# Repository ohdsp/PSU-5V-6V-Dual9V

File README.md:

# [Open Hardware DSP Platform](http://www.ohdsp.org)
## Multi output power supply for OHDSP
### Revision 1.1
###### PSU-5V-6V-Dual9V (KiCad 4.0.2-stable)
---
# README
### Disclaimer
Copyright Paul Janicki 2016

Licensed under the TAPR Open Hardware License (www.tapr.org/OHL)

This documentation is distributed WITHOUT ANY EXPRESS OR IMPLIED WARRANTY, INCLUDING OF MERCHANTABILITY, SATISFACTORY QUALITY AND FITNESS FOR A PARTICULAR PURPOSE.

### What is this repository? ###

**Quick summary**

This is a power supply for use with OHDSP boards.

This power supply requires a single 9Vac input (around 500mA should be sufficient for simple systems). 

This power supply outputs one 5V, one 5V or 6V, and +/-9V. Be warned that each of the 5V and 6V rail should be able to deliver higher currents (up to 1A) without issue, but this will overload the input if you are not careful.

This repository contains the KiCad design files, manufacturing Gerber/drill files, and PDF/drawing files for this board.

### How do I get set up? ###

**Summary of set up**

1. Set your self up a directory on a local disk, something simple will make life easier (eg C:\Electronics on Windows as used here), but anywhere will do just fine.
2. Download the Kicad-Libs from [https://github.com/ohdsp/KiCad-Libs](https://github.com/ohdsp/KiCad-Libs) and place in C:\Electronics\Kicad-Libs (or your chosen folder)  
3. Create a OHDSP subdirectory in C:\Electronics (so C:\Electronics\OHDSP)
3. Download this project to C:\Electronics\OHDSP\PSU-5V-6V-Dual9V
4. Fire up Kicad
5. Open the main project file C:\Electronics\OHDSP\PSU-5V-6V-Dual9V\Schematics\PSU-5V-6V-Dual9V.pro
6. (Optional) Setup Pcbnew component library as below.
7. Do as you wish with the project, just keep it under TAPR Open Hardware License

Make sure your git setup doesn't exclude files used in the project (like .LIB files) or things may go wrong down the line.

**KiCad Library Configuration**

Note that you need to setup a Pcbnew library, but the eeschema libraries should work without any changes if you followed the instructions above.

To setup Pcbnew libraries:

In Pcbnew go to Preferences -> Footprint Libraries Manager. Under Global Libraries tab in the top list check if there is a nickname "MyKiCadLibs-Footprints" (usually at the end of the list). If there is but it points to the wrong place then change the Library Path to point to MyKiCadLibs-Footprints (eg C:\Electronics\KiCad-Libs\MyKiCadLibs-Footprints.pretty) folder for your setup. If this is missing you can use "Append with Wizard", choose "Files on my computer", click next, browse to library location (eg C:\Electronics\KiCad-Libs\MyKiCadLibs-Footprints.pretty) and select the folder MyKiCadLibs-Footprints.pretty, click next, check the Status column states OK and the Format is KiCad (if not re-download the library) and click next, then select "To global library configuration..." and click Finish.

To setup eeschema component libraries:
Either from KiCad project window go to Tools -> Run Library Editor OR under eeschema, go to Tools -> Library Editor. Then Preferences -> Component Libraries.

The top section "Component Library Files" should ideally contain only two libraries, the "power" library that ships with KiCad and "MyKiCadLibs-Lib" available from above. To setup MyKiCadLibs-Lib as a relative path under the "User defined search path" click add. Browse to the location of KiCad-Libs you download above (eg C:\Electronics\KiCad-Libs) and click "Select Folder". Say yes to add a relative path. Under component library files click add, browse to the KiCad-libs again (eg C:\Electronics\KiCad-Libs), select file "MyKiCadLibs-Lib.lib" and click open. MyKiCadLibs-lib should appear in the component library list with no path as it will be using the user defined search path set in the box below.

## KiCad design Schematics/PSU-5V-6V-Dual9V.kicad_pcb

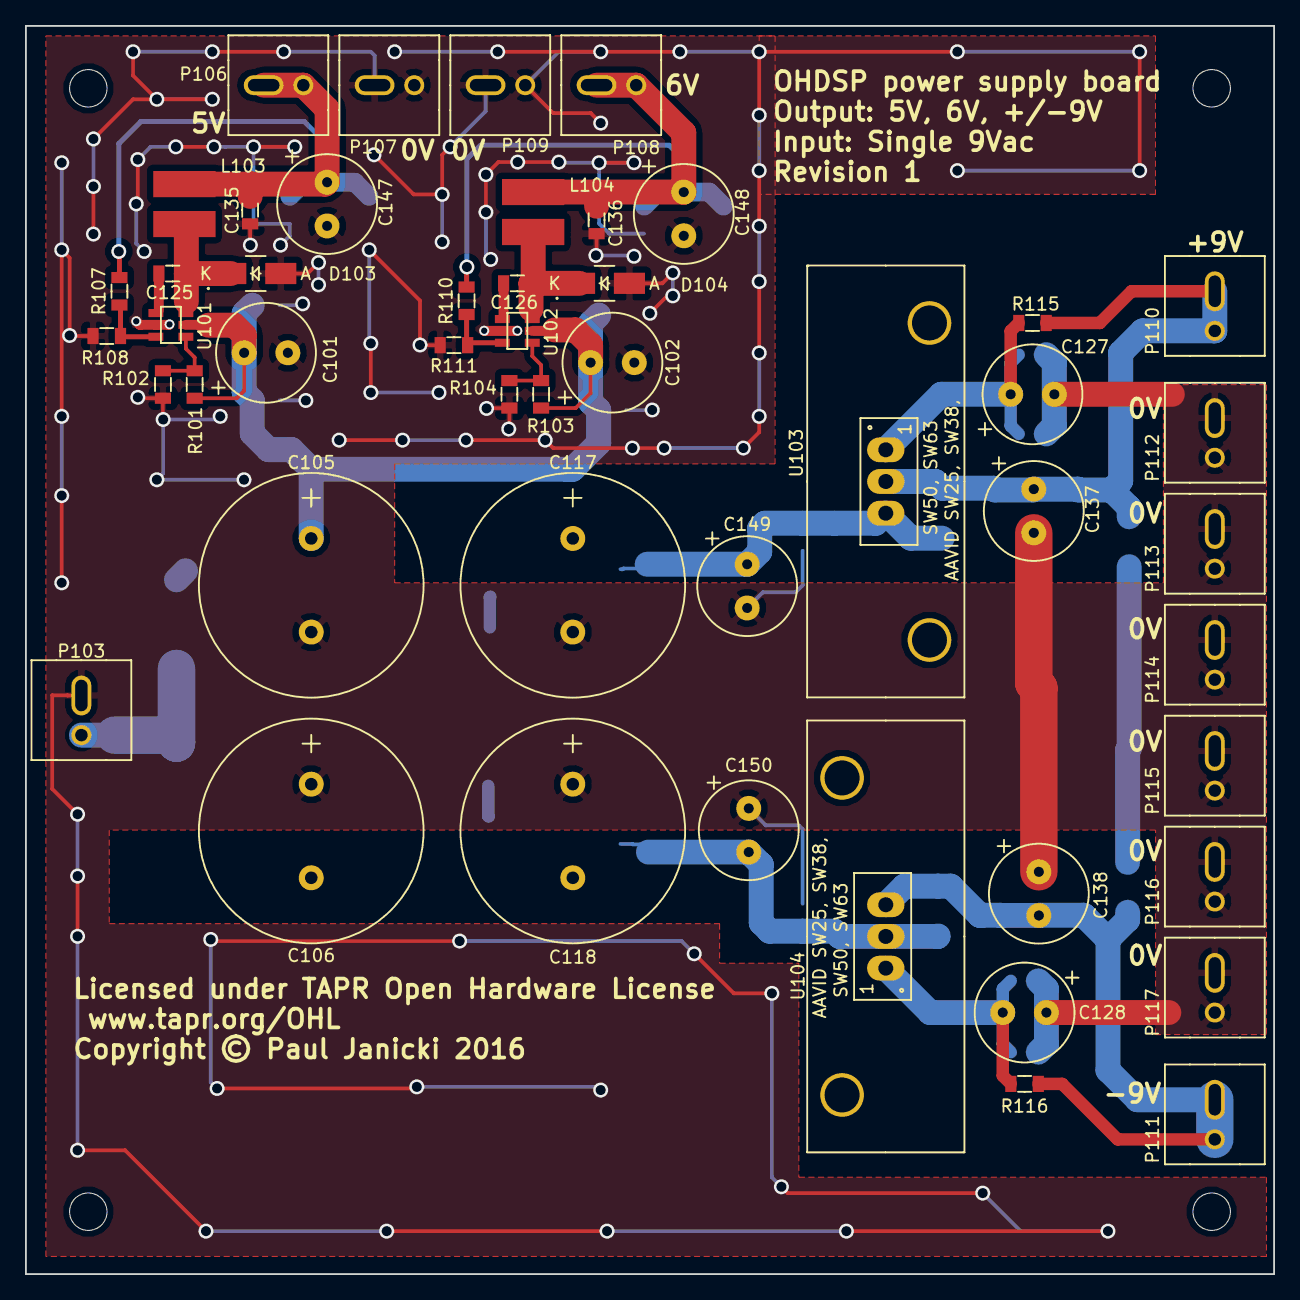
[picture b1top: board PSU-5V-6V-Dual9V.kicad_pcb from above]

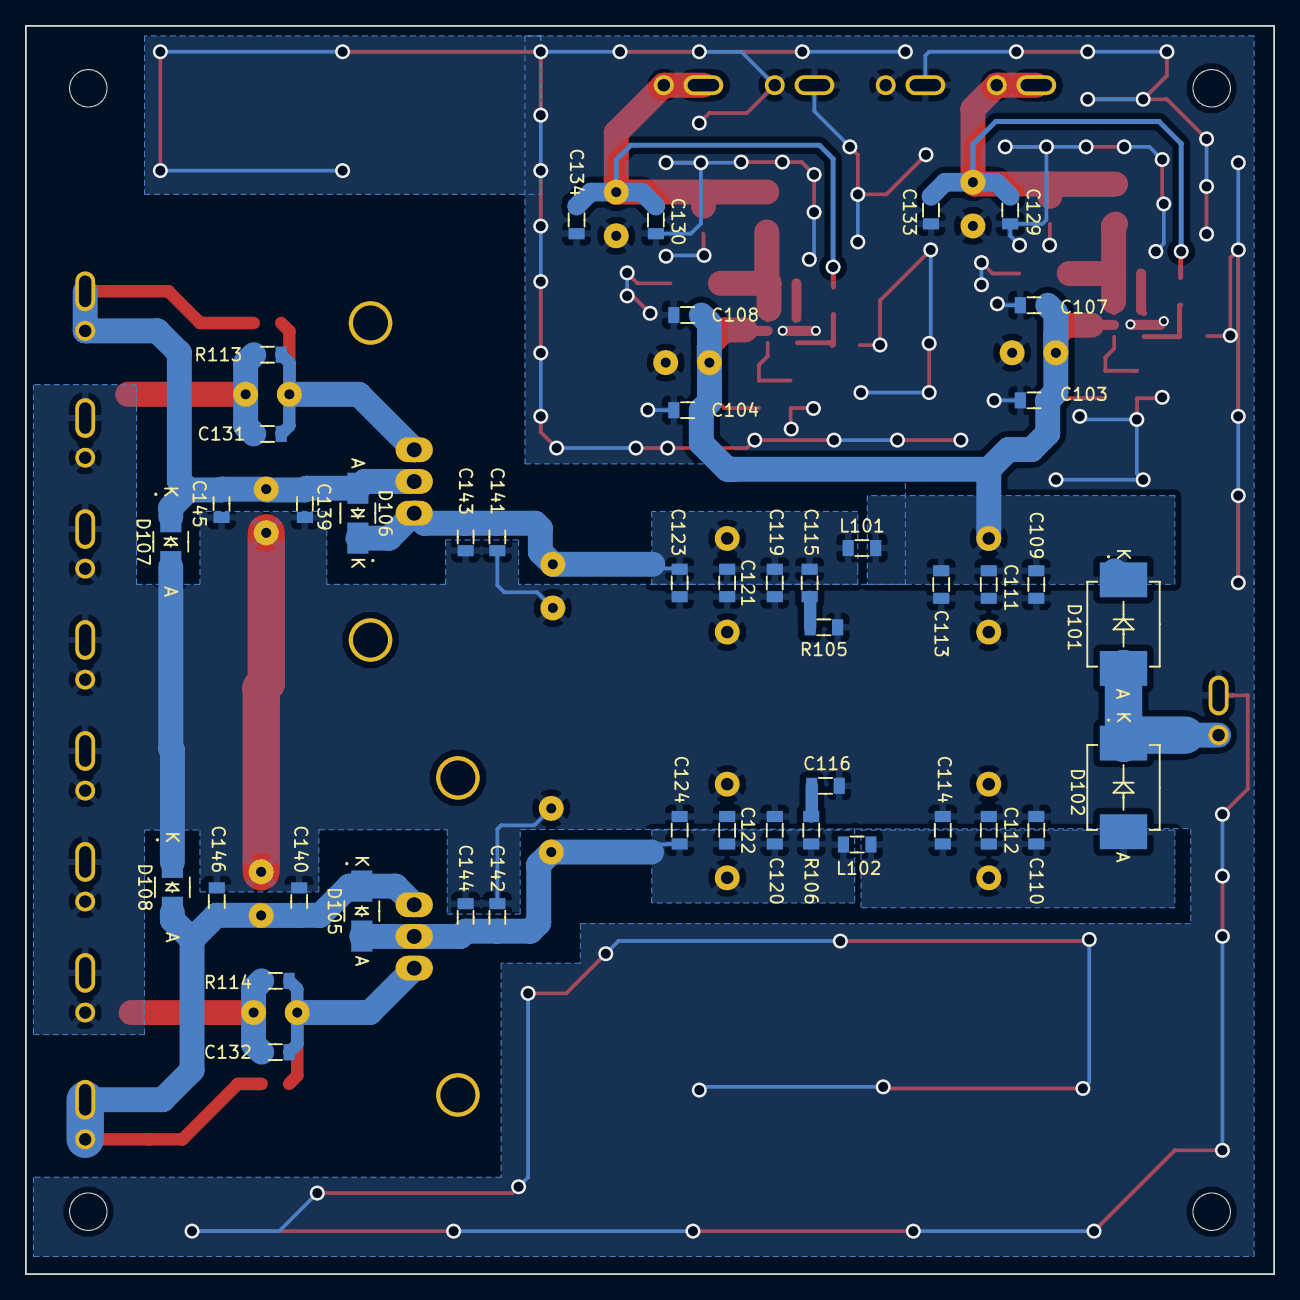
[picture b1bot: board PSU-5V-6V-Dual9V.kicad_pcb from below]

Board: 2 copper layers, 100.0 x 100.0 mm, 97 parts (44 on the bottom side), 22 nets.

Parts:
C101, C102, C127, C128, C137, C138, C147, C148, C149, C150: 220u; CAP-TH-D8mmP3.5mm
C103, C104, C109, C110, C119, C120, C129, C130, C133, C134, C141, C142, C145, C146: 22u; SMD-0805
C105, C106, C117, C118: 2200u; CAP-TH-D18mmP7.5mm
C107, C108, C111, C112, C121, C122, C131, C132, C135, C136, C139, C140, C143, C144: 100n; SMD-0805
C113, C114, C123, C124, C125, C126: 10n; SMD-0805
C115, C116: 100p; SMD-0805
D101, D102: ES3D; DIODE-SMC
D103, D104, D105, D106, D107, D108: B230A; DIODE-SMA
L101, L102: 600R@100MHz; SMD-0805
L103, L104: VLC5045T-6R8M; IND-VLC4045
P101, P102, P104, P105: PIN; MountingHole_3mm
P103, P106, P107, P108, P109, P110, P111, P112, P113, P114, P115, P116, P117: CONN_2x1; CONN-2WAY-2.54mm-3.81mm-SPACING
R101, R102: R; SMD-0805
R103: 475k; SMD-0805
R104: 100k; SMD-0805
R105, R106: 47R; SMD-0805
R107: 53k6; SMD-0805
R108, R111: 10k; SMD-0805
R110: 66k5; SMD-0805
R113, R114: 750; SMD-0805
R115, R116: 120; SMD-0805
U101, U102: ADP2301AUJZ; IC-SOT23-6
U103: IC-REG-LM317-TO220; IC-TO220-HS-SW25-2G
U104: IC-REG-LM337-TO220; IC-TO220-HS-SW25-2G

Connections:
GNDA: C101.2, C102.2, C103.2, C104.2, C105.2, C106.1, C107.2, C108.2, C109.2, C110.1, C111.2, C112.1, C113.2, C114.1, C116.1, C117.2, C118.1, C119.2, C120.1, C121.2, C122.1, C123.2, C124.1, C127.2, C128.1, C129.2, C130.2, C131.2, C132.1, C133.2, C134.2, C135.2, C136.2, C137.2, C138.1, C139.2, C140.1, C141.2, C142.1, C143.2, C144.1, C145.2, C146.1, C147.2, C148.2, C149.2, C150.1, D103.1, D104.1, D107.1, D108.2, P103.2, P107.1, P107.2, P109.1, P109.2, P112.1, P112.2, P113.1, P113.2, P114.1, P114.2, P115.1, P115.2, P116.1, P116.2, P117.1, P117.2, R102.2, R104.2, R105.2, R108.1, R111.1, R113.1, R114.2, U101.2, U102.2
unnamed: C106.2, C110.2, C112.2, C114.2, D102.1, L102.1
unnamed: C115.1, C117.1, C119.1, C121.1, C123.1, C141.1, C143.1, C149.1, D106.2, L101.2, U103.3
unnamed: C115.2, R105.1
unnamed: C116.2, R106.1
unnamed: C118.2, C120.2, C122.2, C124.2, C142.2, C144.2, C150.2, D105.1, L102.2, R106.2, U104.2
unnamed: C125.1, D103.2, L103.1, U101.6
unnamed: C125.2, U101.1
unnamed: C126.1, D104.2, L104.1, U102.6
unnamed: C126.2, U102.1
unnamed: C127.1, C131.1, R113.2, R115.1, U103.1
unnamed: C128.2, C132.2, R114.1, R116.1, U104.1
unnamed: C129.1, C133.1, C135.1, C147.1, L103.2, P106.1, P106.2, R107.1
unnamed: C130.1, C134.1, C136.1, C148.1, L104.2, P108.1, P108.2, R110.1
unnamed: C137.1, C139.1, C145.1, D106.1, D107.2, P110.1, P110.2, R115.2, U103.2
unnamed: C138.2, C140.2, C146.2, D105.2, D108.1, P111.1, P111.2, R116.2, U104.3
unnamed: D101.1, D102.2, P103.1
unnamed: R101.1, R102.1, U101.4
unnamed: R103.1, R104.1, U102.4
unnamed: R107.2, R108.2, U101.3
unnamed: R110.2, R111.2, U102.3
VCC: C101.1, C102.1, C103.1, C104.1, C105.1, C107.1, C108.1, C109.1, C111.1, C113.1, D101.2, L101.1, R101.2, R103.2, U101.5, U102.5

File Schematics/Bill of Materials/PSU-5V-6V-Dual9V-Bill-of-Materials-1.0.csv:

,PSU-5V-6V-Dual9V Bill of Materials Release 1.0,,,,,,
,"24/01/16",,,,,,
"Id","Designator","Package","Quantity","Designation","Detail",,
1,"C101,C102,C127,C128,C137,C138,C147,C148,C149,C150","CAP-TH-D8mmP3.5mm",10,"220u","'=>25V eg Panasonic EEU-FC1V221L",,
2,"C103,C104,C109,C110,C119,C120,C129,C130,C133,C134,C141,C142,C145,C146","SMD-0805",14,"22u","25V X5R 20%",,
3,"C105,C106,C117,C118","CAP-TH-D18mmP7.5mm",4,"2200u","'=>25V eg Panasonic EEU-FC1V222",,
4,"C107,C108,C111,C112,C121,C122,C131,C132,C135,C136,C139,C140,C143,C144","SMD-0805",14,"100n","50V X7R 10%",,
5,"C113,C114,C123,C124,C125,C126","SMD-0805",6,"10n","50V X7R 10%",,
6,"C115,C116","SMD-0805",2,"100p","50V NP0 5%",,
7,"D101,D102","DIODE-SMC",2,"ES3D","Diode Inc ES3D, Vishay ES3D-E3/57T - 3A 200V Ultrafast",,
8,"D103,D104,D105,D106,D107,D108","DIODE-SMA",6,"B230A","Diodes Inc. B230A-13-F",,
9,"L101,L102","SMD-0805",2,"600R@100MHz","'=>1A eg Wruth 742792040, TDK MPZ2012S601A",,
10,"L103,L104","IND-VLC4045",2,"VLC5045T-6R8M",TDK VLC5045T-6R8M 6.8uH 46mOhm 2.7A SMD inductor,,
11,"P101,P102,P104,P105","MountingHole_3mm",4,"PIN","Mounting hole only",,
12,"P103,P106,P107,P108,P109,P110,P111,P112,P113,P114,P115,P116,P117","CONN-2WAY-2.54mm-3.81mm-SPACING",13,"CONN_2x1","Any 2.54mm  or 3.81mm screw terminal eg CamdenBoss CTB0308/2",,
13,"R101,R102","SMD-0805",2,"R","R101 is 475k, R102 is 100k - 100mW",,
14,"R103","SMD-0805",1,"475k","100mW",,
15,"R104","SMD-0805",1,"100k","100mW",,
16,"R105,R106","SMD-0805",2,"47R","100mW",,
17,"R107","SMD-0805",1,"53k6","100mW",,
18,"R108,R111","SMD-0805",2,"10k","100mW",,
19,"R110","SMD-0805",1,"66k5","100mW",,
20,"R113,R114","SMD-0805",2,"750","250mW",,
21,"R115,R116","SMD-0805",2,"120","250mW",,
22,"U101,U102","IC-SOT23-6",2,"ADP2301AUJZ","Analog Devices ADP2301AUJZ DC-DC Step-Down",,
23,"U103","IC-TO220-HS-SW25-2G",1,"IC-REG-LM317-TO220","LM317 TO220 package - eg On Semi LM317TG",,
24,"U104","IC-TO220-HS-SW25-2G",1,"IC-REG-LM337-TO220","LM337 TO220 package - eg On Semi LM337TG",,

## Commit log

2016-01-24 Release 1.0
    Release 1.0
2016-05-22 Revision 1.1
2016-07-01 Revision 2.0
    Update BOM sheet name
2016-07-01 Revert "Revision 2.0"
    This reverts commit c2e791a39c248d66cfa27da6c09bcea51845a439.
2016-07-01 Revision 1.1
    Update BOM sheet name

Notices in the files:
Schematics/PSU-5V-6V-Dual9V.kicad_pcb:
Licensed under TAPR Open Hardware License
Copyright © Paul Janicki 2016
